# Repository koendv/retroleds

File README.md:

This is a 16x2 serial character display using the following HP/Avago/Broadcom LEDs:

HDSP-2107 HDSP-2112 HDSP-2110 HDSP-2111 HDSP-2113
          HDSP-2122           HDSP-2121 HDSP-2123 

Inform me if other LED displays work too.

The display consists of a pcb board and an arduino sketch.

Any character received on the serial port is shown on the LED display.
The display provides a very complete ASCII character set, including accented characters, Japanese Katakana and Cyrillic. Other 5x7 bitmap fonts can be added if needed.

Optionally, a PS/2 keyboard can be connected. Any key typed on the keyboard is sent to the serial port. Together, display and PS/2 keyboard form a rudimentary serial terminal.

To use the display, a USB to serial adapter and a 5V power supply are needed. Plug a USB to 5V TTL serial cable into the serial port header. The serial port runs at 38400 8N1, no hardware flow control. Plug in a 5V DC 2A power supply, center pin positive, into the barrel jack connector.  Carefully check connector polarity before plugging in.

Escape codes provide simple display control.

Escape Code|Action
-----------|------
Esc[2J|		     Clear screen
Esc[5m|              Turn blinking mode on
Esc[0m|              Turn blinking mode off
Esc[30m ... Esc[37m| Set display brightness, 0 ... 7. 0 = blanked display, 7 = maximum brightness. Default: 3.
Esc[1G ... Esc[33G|  Set cursor position. 1 = top left. 33 = bottom right
Esc[10m|             Select ascii font (default)
Esc[11m|             Select Katakana font
Esc[12m|             Select Cyrillic font
Esc[2;|		     Display test

A blinking question mark '?' indicates an error condition, usually an unrecognized escape code.

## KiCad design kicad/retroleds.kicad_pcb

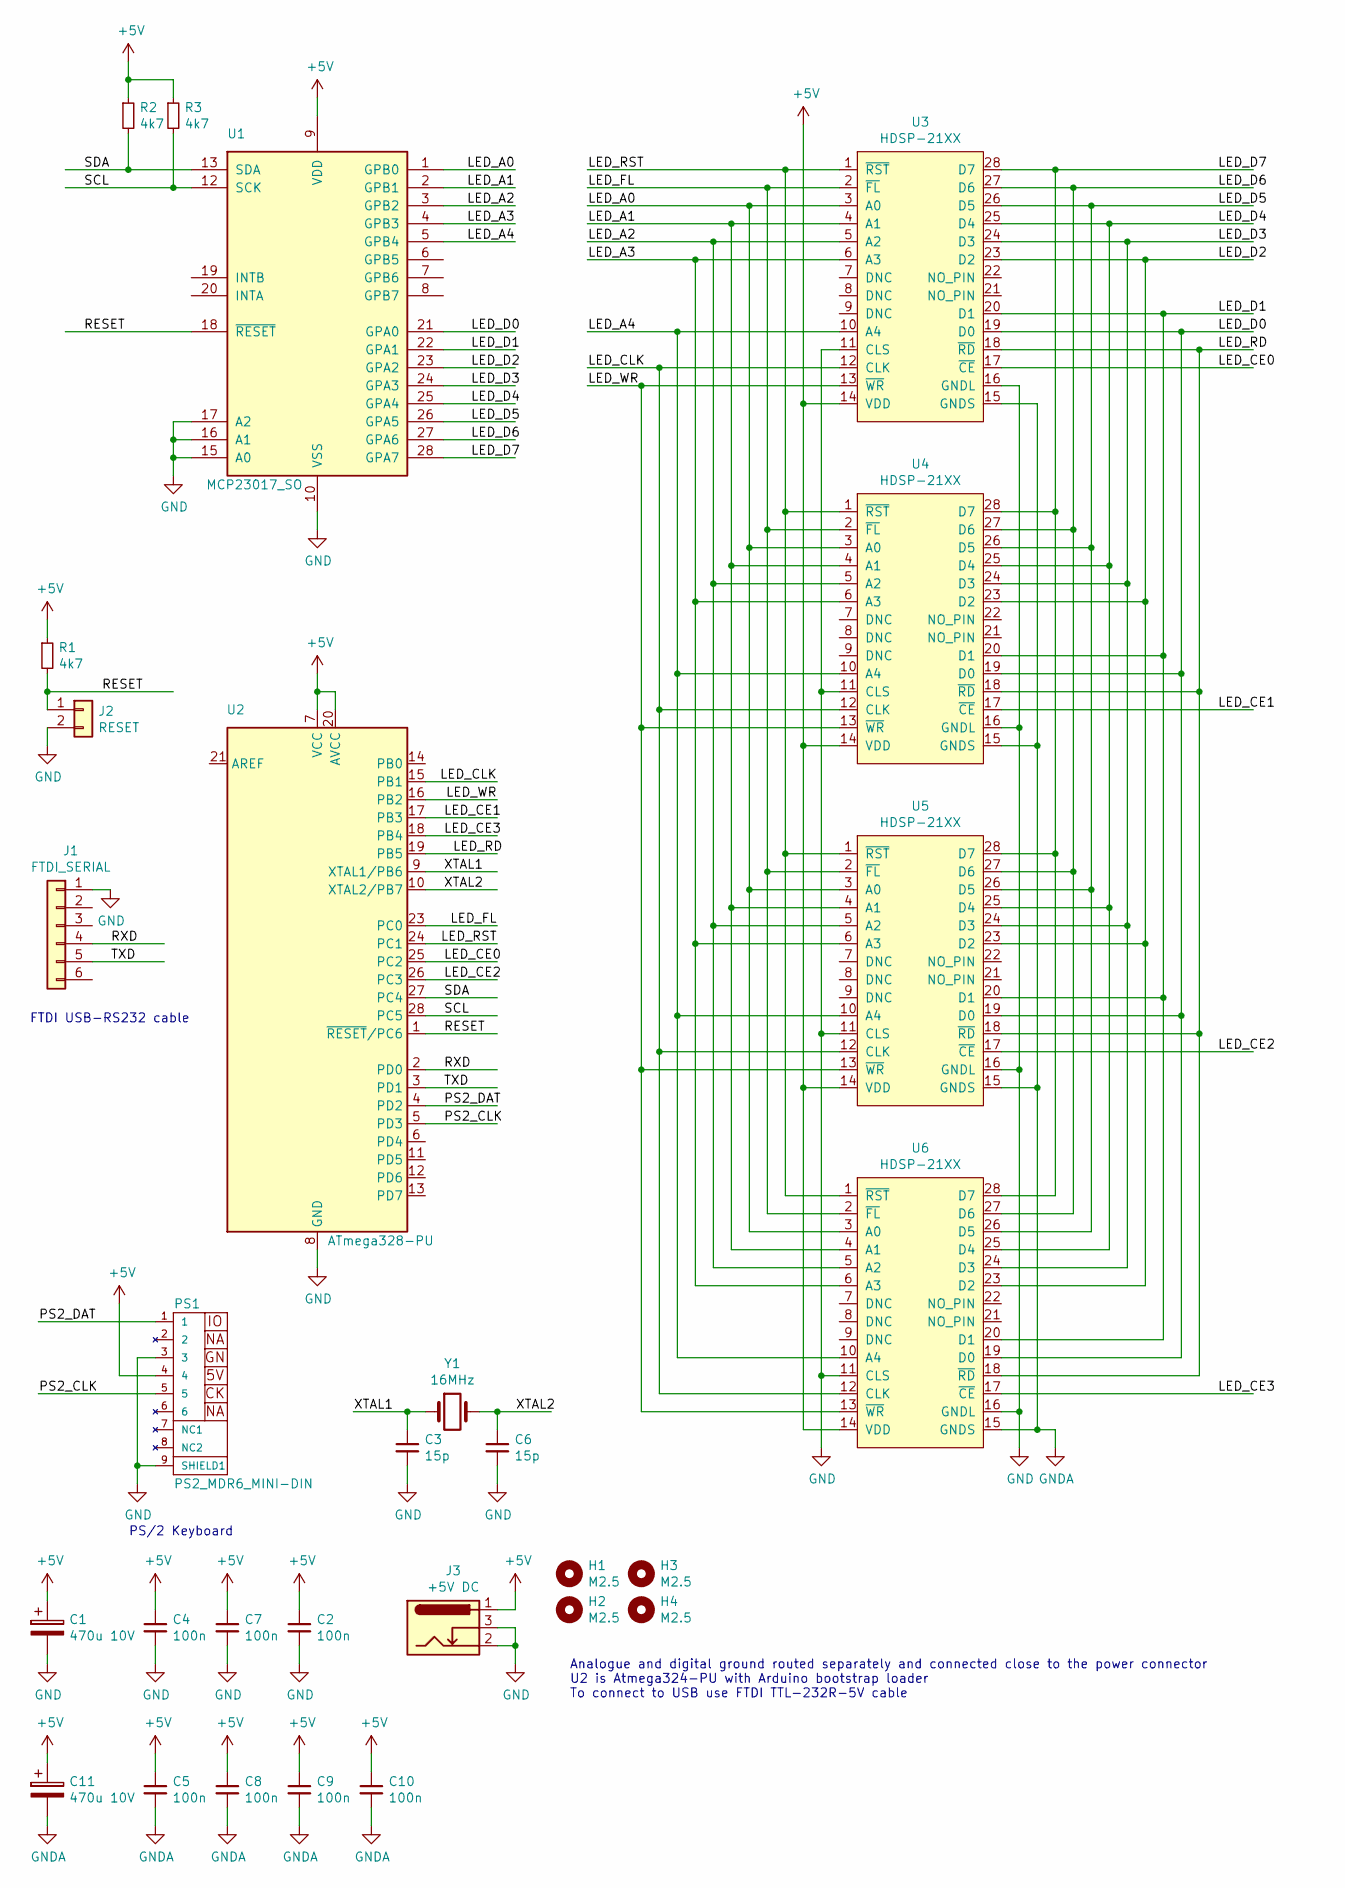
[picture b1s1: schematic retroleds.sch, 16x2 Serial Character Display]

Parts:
C1, C11: 470u 10V; CP_Radial_D7.5mm_P2.50mm
C2, C4, C5, C7, C8, C9, C10: 100n; C_Rect_L4.6mm_W3.0mm_P2.50mm_MKS02_FKP02
C3, C6: 15p; C_Disc_D3.4mm_W2.1mm_P2.50mm
H1, H2, H3, H4: M2.5; MountingHole_2.7mm_M2.5
J1: FTDI_SERIAL; PinHeader_1x06_P2.54mm_Vertical
J2: RESET; PinHeader_1x02_P2.54mm_Vertical
J3: +5V DC; BarrelJack_CUI_PJ-102AH_Horizontal
PS1: PS2_MDR6_MINI-DIN
R1, R2, R3: 4k7; R_Axial_DIN0207_L6.3mm_D2.5mm_P7.62mm_Horizontal
U1: MCP23017_SO; DIP-28_W7.62mm
U2: ATmega328-PU; DIP-28_W7.62mm
U3, U4, U5, U6: HDSP-21XX; HDSP-21xx
Y1: 16MHz; Crystal_HC49-U_Vertical

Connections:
+5V: C1.1, C2.1, C4.1, C5.1, C7.1, C8.1, C9.1, C10.1, C11.1, J3.1, PS1.4, R1.1, R2.1, R3.1, U1.9 (VDD), U2.7 (VCC), U2.20 (AVCC), U3.14 (VDD), U4.14 (VDD), U5.14 (VDD), U6.14 (VDD)
/LED_A0: U1.1 (GPB0), U3.3 (A0), U4.3 (A0), U5.3 (A0), U6.3 (A0)
/LED_A1: U1.2 (GPB1), U3.4 (A1), U4.4 (A1), U5.4 (A1), U6.4 (A1)
/LED_A2: U1.3 (GPB2), U3.5 (A2), U4.5 (A2), U5.5 (A2), U6.5 (A2)
/LED_A3: U1.4 (GPB3), U3.6 (A3), U4.6 (A3), U5.6 (A3), U6.6 (A3)
/LED_A4: U1.5 (GPB4), U3.10 (A4), U4.10 (A4), U5.10 (A4), U6.10 (A4)
/LED_CE0: U2.25 (PC2), U3.17 (~CE)
/LED_CE1: U2.17 (PB3), U4.17 (~CE)
/LED_CE2: U2.26 (PC3), U5.17 (~CE)
/LED_CE3: U2.18 (PB4), U6.17 (~CE)
/LED_CLK: U2.15 (PB1), U3.12 (CLK), U4.12 (CLK), U5.12 (CLK), U6.12 (CLK)
/LED_D0: U1.21 (GPA0), U3.19 (D0), U4.19 (D0), U5.19 (D0), U6.19 (D0)
/LED_D1: U1.22 (GPA1), U3.20 (D1), U4.20 (D1), U5.20 (D1), U6.20 (D1)
/LED_D2: U1.23 (GPA2), U3.23 (D2), U4.23 (D2), U5.23 (D2), U6.23 (D2)
/LED_D3: U1.24 (GPA3), U3.24 (D3), U4.24 (D3), U5.24 (D3), U6.24 (D3)
/LED_D4: U1.25 (GPA4), U3.25 (D4), U4.25 (D4), U5.25 (D4), U6.25 (D4)
/LED_D5: U1.26 (GPA5), U3.26 (D5), U4.26 (D5), U5.26 (D5), U6.26 (D5)
/LED_D6: U1.27 (GPA6), U3.27 (D6), U4.27 (D6), U5.27 (D6), U6.27 (D6)
/LED_D7: U1.28 (GPA7), U3.28 (D7), U4.28 (D7), U5.28 (D7), U6.28 (D7)
/LED_FL: U2.23 (PC0), U3.2 (~FL), U4.2 (~FL), U5.2 (~FL), U6.2 (~FL)
/LED_RD: U2.19 (PB5), U3.18 (~RD), U4.18 (~RD), U5.18 (~RD), U6.18 (~RD)
/LED_RST: U2.24 (PC1), U3.1 (~RST), U4.1 (~RST), U5.1 (~RST), U6.1 (~RST)
/LED_WR: U2.16 (PB2), U3.13 (~WR), U4.13 (~WR), U5.13 (~WR), U6.13 (~WR)
/PS2_CLK: PS1.5, U2.5 (PD3)
/PS2_DAT: PS1.1, U2.4 (PD2)
/RESET: J2.1, R1.2, U1.18 (~RESET~), U2.1 (~RESET~/PC6)
/RXD: J1.4, U2.2 (PD0)
/SCL: R3.2, U1.12 (SCK), U2.28 (PC5)
/SDA: R2.2, U1.13 (SDA), U2.27 (PC4)
/TXD: J1.5, U2.3 (PD1)
/XTAL1: C3.1, U2.9 (XTAL1/PB6), Y1.1
/XTAL2: C6.1, U2.10 (XTAL2/PB7), Y1.2
GND: C1.2, C2.2, C3.2, C4.2, C6.2, C7.2, J1.1, J2.2, J3.2, J3.3, PS1.3, PS1.9 (SHIELD1), U1.10 (VSS), U1.15 (A0), U1.16 (A1), U1.17 (A2), U2.8 (GND), U2.22 (GND), U3.11 (CLS), U3.16 (GNDL), U4.11 (CLS), U4.16 (GNDL), U5.11 (CLS), U5.16 (GNDL), U6.11 (CLS), U6.16 (GNDL)
GNDA: C5.2, C8.2, C9.2, C10.2, C11.2, U3.15 (GNDS), U4.15 (GNDS), U5.15 (GNDS), U6.15 (GNDS)

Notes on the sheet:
Analogue and digital ground routed separately and connected close to the power connector U2 is Atmega324-PU with Arduino bootstrap loader To connect to USB use FTDI TTL-232R-5V cable
FTDI USB-RS232 cable
PS/2 Keyboard

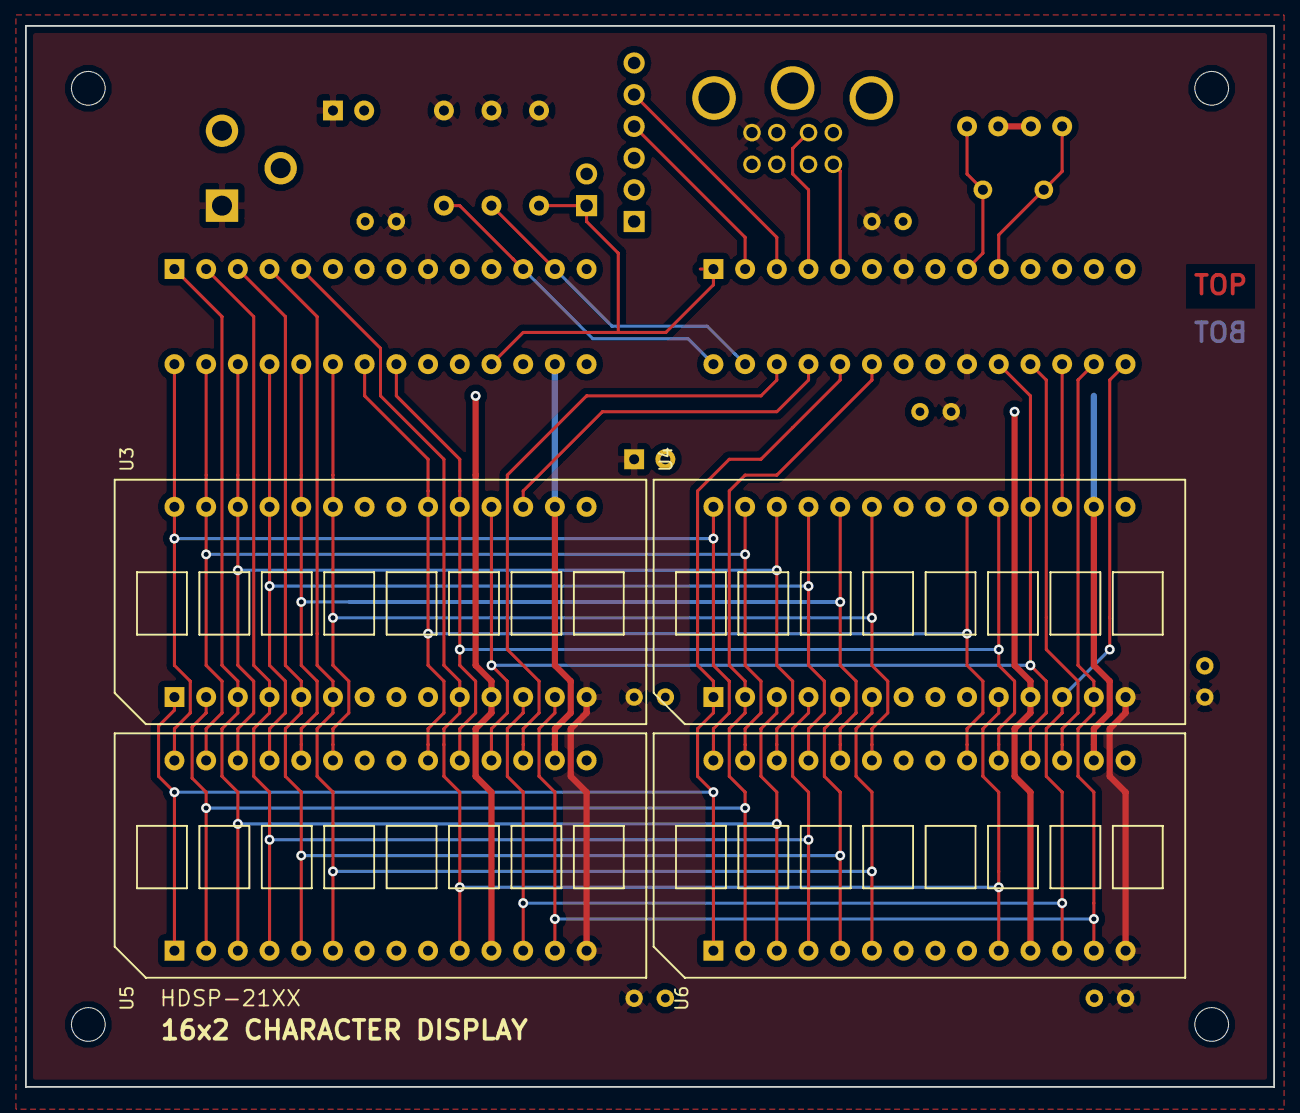
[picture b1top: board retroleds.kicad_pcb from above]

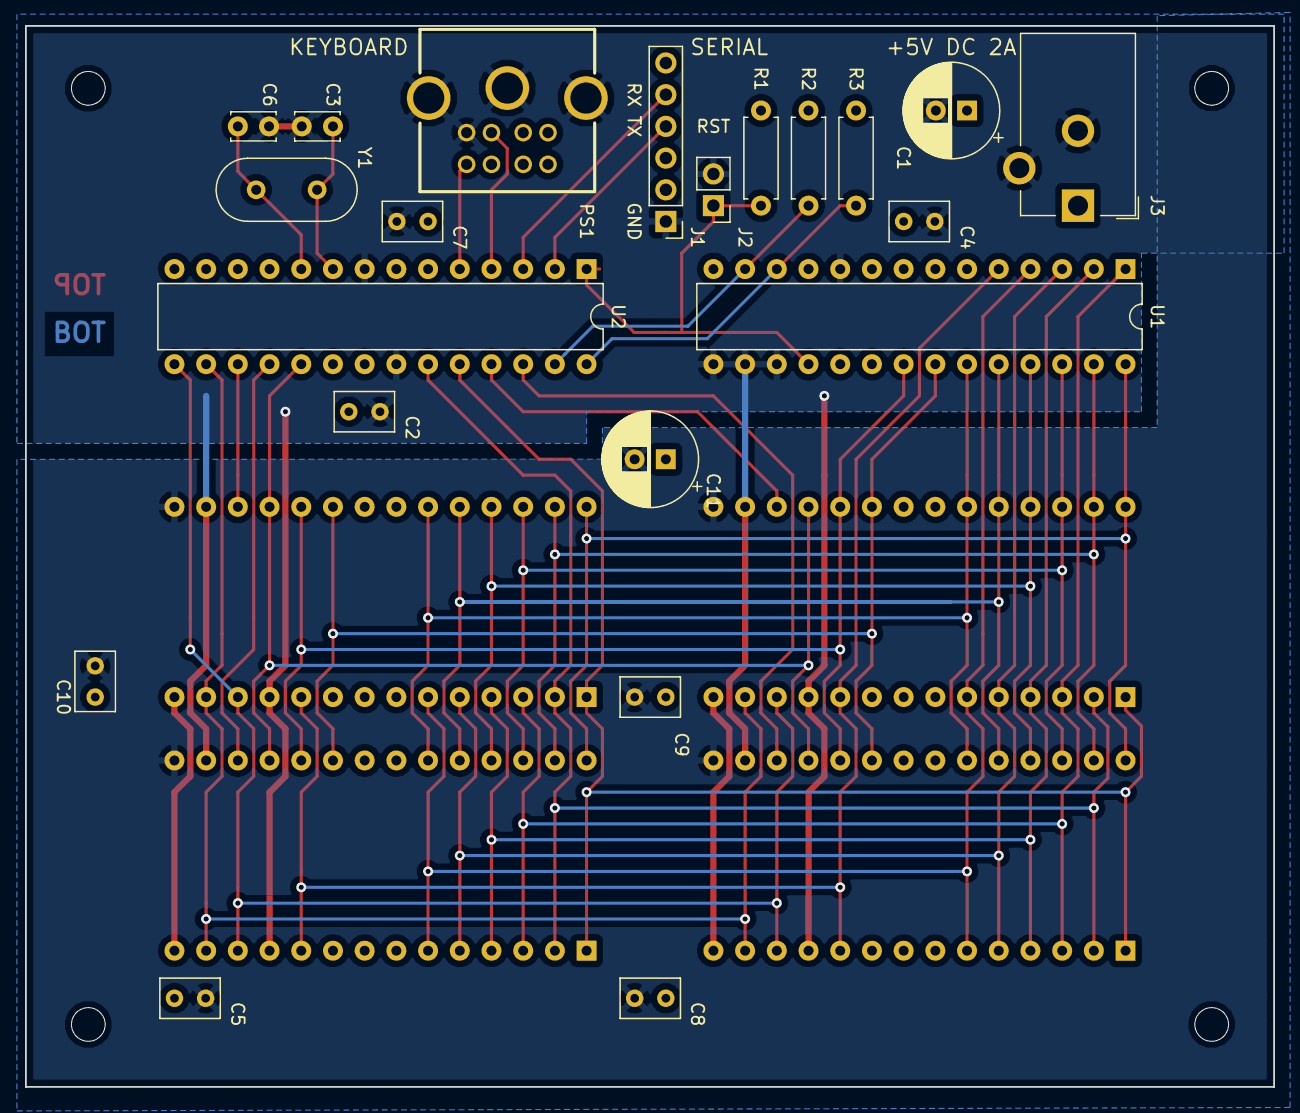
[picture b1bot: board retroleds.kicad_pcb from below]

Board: 2 copper layers, 100.0 x 85.0 mm, 29 parts (21 on the bottom side), 34 nets.

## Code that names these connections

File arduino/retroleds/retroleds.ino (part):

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
/* pins on atmega328p */

#define LED_CE0  16
#define LED_CE1  11
#define LED_CE2  17
#define LED_CE3  12
#define LED_CLK  9
#define LED_FL   14
#define LED_RD   13
#define LED_RST  15
#define LED_WR   10
#define PS2_CLK  3
#define PS2_DAT  2

Adafruit_MCP23017 mcp;
PS2Keyboard keyboard;
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  // configure TIMER 1 for frequency of 57348 Hz.
  Timer1.initialize(17);  // set PWM period to 17 us = 58.8 kHz

  // set LED_CLK output pin to 50% duty cycle
  Timer1.pwm(LED_CLK, 511);
  
  return;
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void setup() {

  /* pins on atmega */ 
  pinMode(LED_CE0, OUTPUT);
  pinMode(LED_CE1, OUTPUT);
  pinMode(LED_CE2, OUTPUT);
  pinMode(LED_CE3, OUTPUT);
  pinMode(LED_CLK, OUTPUT);
  pinMode(LED_FL, OUTPUT);
  pinMode(LED_RD, OUTPUT);
  pinMode(LED_RST, OUTPUT);
  pinMode(LED_WR, OUTPUT);
  digitalWrite(LED_CE0, HIGH);
  digitalWrite(LED_CE1, HIGH);
  digitalWrite(LED_CE2, HIGH);
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
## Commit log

2019-03-17 font dump
2019-03-18 better pdf
2019-07-20 arduino
2019-07-21 esc codes
2019-08-11 add display test
2019-08-12 speedup
2019-08-12 cursor fix
2019-08-13 cls optimize

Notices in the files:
arduino/retroleds/retroleds.ino:
Copyright (c) 2019 Koen De Vleeschauwer.  All rights reserved.
